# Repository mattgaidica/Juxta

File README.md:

# Juxta
 
__TI CCS Dev__

> Use LP_CC1352P7_4 projects for your CC2652P7 device.  This is also covered in the Running Software Examples on CC2652P module of the BLE5-Stack Migration Guide.  You still need an antenna switch to determine whether to use the normal or high-PA output path, although if using a custom design with one determined path then you can choose "Use Custom Board" and remove the CONFIG_RF_* pin assignments.

* In CCS > *.syscfg click the Board icon, select "Use custom board"
* Make a new target file for CC2652P7 and right-click it active

${COM_TI_SIMPLELINK_CC13XX_CC26XX_SDK_INSTALL_DIR_REPOS}

__Base SysConfig (no RF)__

		/**
	 * These arguments were used when this file was generated. They will be automatically applied on subsequent loads
	 * via the GUI or CLI. Run CLI with '--help' for additional information on how to override these arguments.
	 * @cliArgs --device "CC1352P7RGZ" --package "RGZ" --part "Default" --rtos "tirtos7" --product "simplelink_cc13xx_cc26xx_sdk@6.10.00.29"
	 * @versions {"tool":"1.12.0+2406"}
	 */
	
	/**
	 * Import the modules used in this configuration.
	 */
	const rfdesign    = scripting.addModule("/ti/devices/radioconfig/rfdesign");
	const ADC         = scripting.addModule("/ti/drivers/ADC", {}, false);
	const ADC1        = ADC.addInstance();
	const GPIO        = scripting.addModule("/ti/drivers/GPIO");
	const GPIO2       = GPIO.addInstance();
	const GPIO3       = GPIO.addInstance();
	const GPIO4       = GPIO.addInstance();
	const GPIO5       = GPIO.addInstance();
	const GPIO6       = GPIO.addInstance();
	const GPIO7       = GPIO.addInstance();
	const GPIO8       = GPIO.addInstance();
	const Power       = scripting.addModule("/ti/drivers/Power");
	const SPI         = scripting.addModule("/ti/drivers/SPI", {}, false);
	const SPI1        = SPI.addInstance();
	const Settings    = scripting.addModule("/ti/posix/tirtos/Settings");
	const BIOS        = scripting.addModule("/ti/sysbios/BIOS");
	const Event       = scripting.addModule("/ti/sysbios/knl/Event");
	const Idle        = scripting.addModule("/ti/sysbios/knl/Idle", {}, false);
	const Idle2       = Idle.addInstance();
	const Mailbox     = scripting.addModule("/ti/sysbios/knl/Mailbox");
	const Error       = scripting.addModule("/ti/sysbios/runtime/Error");
	const SysCallback = scripting.addModule("/ti/sysbios/runtime/SysCallback");
	const Timestamp   = scripting.addModule("/ti/sysbios/runtime/Timestamp");
	
	/**
	 * Write custom configuration values to the imported modules.
	 */
	rfdesign.fbSub1g = "none";
	rfdesign.fe24g   = "ID";
	rfdesign.pa20    = "none";
	
	ADC1.$name              = "VBATT";
	ADC1.adc.adcPin.$assign = "DIO_27";
	
	GPIO2.$name           = "LED_1";
	GPIO2.mode            = "Output";
	GPIO2.outputStrength  = "Low";
	GPIO2.gpioPin.$assign = "DIO_6";
	
	GPIO3.$name              = "AXY_CS";
	GPIO3.mode               = "Output";
	GPIO3.initialOutputState = "High";
	GPIO3.gpioPin.$assign    = "DIO_16";
	
	GPIO4.$name           = "AXY_INT";
	GPIO4.pull            = "Pull Up";
	GPIO4.gpioPin.$assign = "DIO_17";
	
	GPIO5.$name           = "DEBUG";
	GPIO5.gpioPin.$assign = "DIO_22";
	
	GPIO6.$name           = "Rx";
	GPIO6.gpioPin.$assign = "DIO_24";
	
	GPIO7.$name           = "Tx";
	GPIO7.mode            = "Output";
	GPIO7.gpioPin.$assign = "DIO_25";
	
	GPIO8.$name           = "LED_0";
	GPIO8.mode            = "Output";
	GPIO8.outputStrength  = "Low";
	GPIO8.gpioPin.$assign = "DIO_26";
	
	const CCFG              = scripting.addModule("/ti/devices/CCFG", {}, false);
	CCFG.ccfgTemplate.$name = "ti_devices_CCFG_CCFGCC26XXTemplate0";
	
	SPI1.$name               = "CONFIG_SPI";
	SPI1.spi.sclkPin.$assign = "DIO_19";
	SPI1.spi.misoPin.$assign = "DIO_20";
	SPI1.spi.mosiPin.$assign = "DIO_21";
	
	BIOS.assertsEnabled = false;
	BIOS.heapBaseAddr   = "__primary_heap_start__";
	BIOS.heapEndAddr    = "__primary_heap_end__";
	
	const Hwi           = scripting.addModule("/ti/sysbios/family/arm/m3/Hwi", {}, false);
	Hwi.enableException = false;
	
	const Clock      = scripting.addModule("/ti/sysbios/knl/Clock", {}, false);
	Clock.tickPeriod = 10;
	
	const Timer       = scripting.addModule("/ti/sysbios/family/arm/cc26xx/Timer", {}, false);
	Timer.rtc.$assign = "RTC0";
	
	Idle2.$name   = "powerIdle";
	Idle2.idleFxn = "Power_idleFunc";
	
	const Semaphore            = scripting.addModule("/ti/sysbios/knl/Semaphore", {}, false);
	Semaphore.supportsPriority = false;
	
	const Swi         = scripting.addModule("/ti/sysbios/knl/Swi", {}, false);
	Swi.numPriorities = 6;
	
	const Task             = scripting.addModule("/ti/sysbios/knl/Task", {}, false);
	Task.defaultStackSize  = 512;
	Task.idleTaskStackSize = 512;
	Task.numPriorities     = 6;
	
	Error.policy       = "Error_SPIN";
	Error.printDetails = false;
	
	const System           = scripting.addModule("/ti/sysbios/runtime/System", {}, false);
	System.abortFxn        = "System_abortSpin";
	System.exitFxn         = "System_exitSpin";
	System.extendedFormats = "%f";
	System.supportModule   = "SysCallback";
	
	/**
	 * Pinmux solution for unlocked pins/peripherals. This ensures that minor changes to the automatic solver in a future
	 * version of the tool will not impact the pinmux you originally saw.  These lines can be completely deleted in order to
	 * re-solve from scratch.
	 */
	ADC1.adc.$suggestSolution              = "ADC0";
	SPI1.spi.$suggestSolution              = "SSI0";
	SPI1.spi.dmaRxChannel.$suggestSolution = "DMA_CH3";
	SPI1.spi.dmaTxChannel.$suggestSolution = "DMA_CH4";

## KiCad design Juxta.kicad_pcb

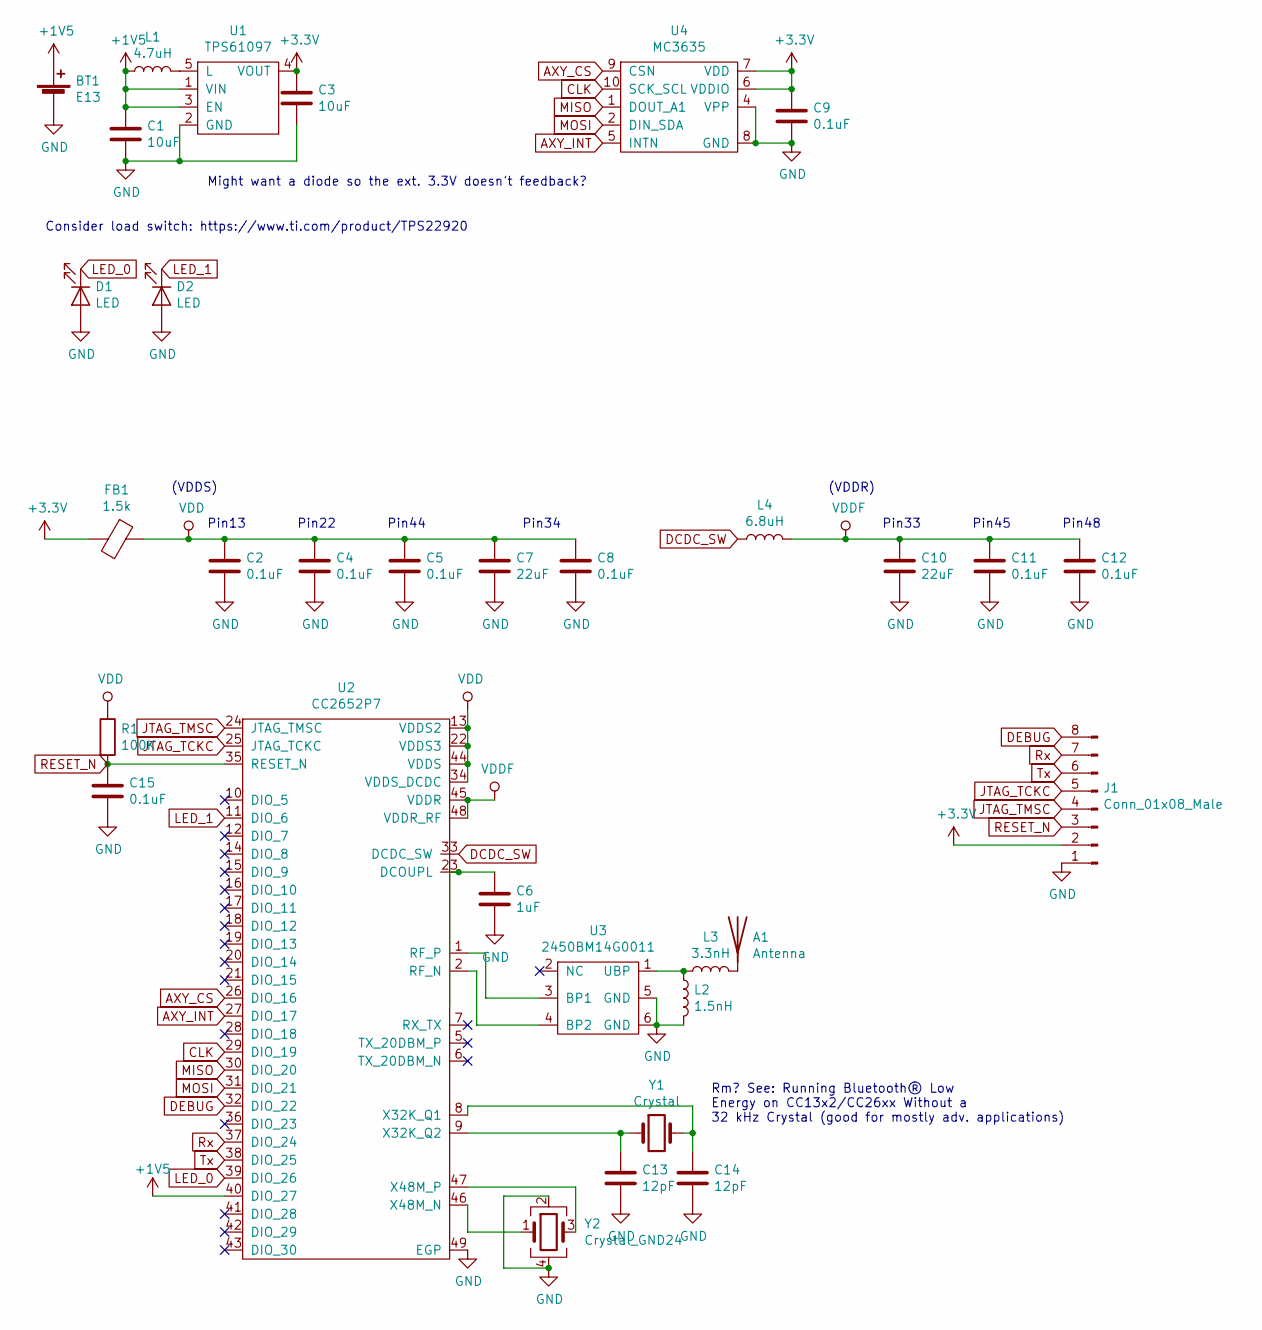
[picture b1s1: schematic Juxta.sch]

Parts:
A1: Antenna; 2450AT18B100; DigiKey 712-1006-1-ND
BT1: E13; 2988_7.9mmBatteryContact; DigiKey 36-2988CT-ND
C1, C3: 10uF; C_0402_1005Metric; DigiKey 13-CC0402MPX5R4BB106CT-ND
C2, C4, C5, C8, C9, C11, C12, C15: 0.1uF; C_0402_1005Metric; DigiKey 478-1126-1-ND
C6: 1uF; C_0402_1005Metric; DigiKey 478-4596-1-ND
C7, C10: 22uF; C_0402_1005Metric; DigiKey 478-04024D226MAT2ACT-ND
C13, C14: 12pF; C_0402_1005Metric; DigiKey 490-5924-2-ND
D1, D2: LED; LED_0402_1005Metric; DigiKey 1830-1056-1-ND
FB1: 1.5k; L_0402_1005Metric; DigiKey 445-2158-1-ND
J1: Conn_01x08_Male; Molex_SlimStack_502430-0820_2x04_P0.40mm_Vertical; Mouser 538-50243-00822
L1: 4.7uH; L_0603_1608Metric; DigiKey 445-6390-1-ND
L2: 1.5nH; L_0402_1005Metric; DigiKey 334-1083-1-ND
L3: 3.3nH; L_0402_1005Metric; DigiKey 490-6561-1-ND
L4: 6.8uH; L_0603_1608Metric; DigiKey 445-MLZ1608M6R8WT000CT-ND
R1: 100K; R_0402_1005Metric; DigiKey RMCF0402FT100KCT-ND
U1: TPS61097; SOT-23-5
U2: CC2652P7; QFN-48-1EP_7x7mm_P0.5mm_EP5.15x5.15mm
U3: 2450BM14G0011; DigiKey 712-1620-1-ND
U4: MC3635; LGA-10_1.6x1.6; DigiKey 2548-MC3635CT-ND
Y1: Crystal; Crystal_SMD_2012-2Pin_2.0x1.2mm; DigiKey SER4081TR-ND
Y2: Crystal_GND24; Crystal_SMD_2016-4Pin_2.0x1.6mm; DigiKey 535-13930-1-ND

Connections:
+1V5: BT1.1 (+), C1.1, L1.1, U1.1 (VIN), U1.3 (EN), U2.40 (DIO_27)
+3V3: C3.1, C9.1, FB1.2, J1.2, U1.4 (VOUT), U4.6 (VDDIO), U4.7 (VDD)
AXY_CS: U2.26 (DIO_16), U4.9 (CSN)
AXY_INT: U2.27 (DIO_17), U4.5 (INTN)
CLK: U2.29 (DIO_19), U4.10 (SCK_SCL)
DCDC_SW: L4.1, U2.33 (DCDC_SW)
DEBUG: J1.8, U2.32 (DIO_22)
GND: BT1.2 (-), C1.2, C2.2, C3.2, C4.2, C5.2, C6.2, C7.2, C8.2, C9.2, C10.2, C11.2, C12.2, C13.2, C14.2, C15.2, D1.2 (A), D2.2 (A), J1.1, L2.2, U1.2 (GND), U2.49 (EGP), U3.5 (GND), U3.6 (GND), U4.4 (VPP), U4.8 (GND), Y2.2, Y2.4
JTAG_TCKC: J1.5, U2.25 (JTAG_TCKC)
JTAG_TMSC: J1.4, U2.24 (JTAG_TMSC)
LED_0: D1.1 (K), U2.39 (DIO_26)
LED_1: D2.1 (K), U2.11 (DIO_6)
MISO: U2.30 (DIO_20), U4.1 (DOUT_A1)
MOSI: U2.31 (DIO_21), U4.2 (DIN_SDA)
unnamed: A1.1, L3.2
unnamed: C6.1, U2.23 (DCOUPL)
unnamed: C13.1, U2.9 (X32K_Q2), Y1.1
unnamed: C14.1, U2.8 (X32K_Q1), Y1.2
unnamed: L1.2, U1.5 (L)
unnamed: L2.1, L3.1, U3.1 (UBP)
unnamed: U2.1 (RF_P), U3.3 (BP1)
unnamed: U2.2 (RF_N), U3.4 (BP2)
unnamed: U2.46 (X48M_N), Y2.1
unnamed: U2.47 (X48M_P), Y2.3
RESET_N: C15.1, J1.3, R1.2, U2.35 (RESET_N)
Rx: J1.7, U2.37 (DIO_24)
Tx: J1.6, U2.38 (DIO_25)
VDD: C2.1, C4.1, C5.1, C7.1, C8.1, FB1.1, R1.1, U2.13 (VDDS2), U2.22 (VDDS3), U2.34 (VDDS_DCDC), U2.44 (VDDS)
VDDF: C10.1, C11.1, C12.1, L4.2, U2.45 (VDDR), U2.48 (VDDR_RF)

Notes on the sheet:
(VDDS)
(VDDR)
Pin33
Pin45
Pin48
Pin34
Pin44
Pin22
Pin13
Might want a diode so the ext. 3.3V doesn’t feedback?
Rm? See: Running Bluetooth® Low Energy on CC13x2/CC26xx Without a 32 kHz Crystal (good for mostly adv. applications)
Consider load switch: https://www.ti.com/product/TPS22920

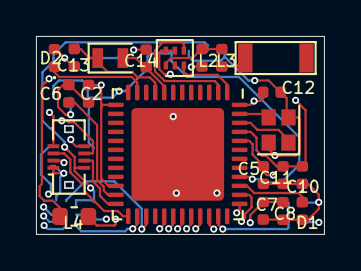
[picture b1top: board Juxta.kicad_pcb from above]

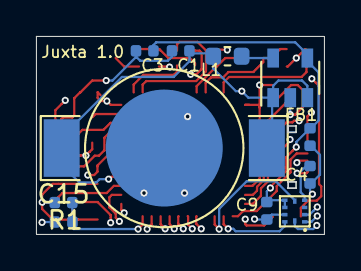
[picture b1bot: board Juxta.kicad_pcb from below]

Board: 4 copper layers, 15.9 x 11.0 mm, 32 parts (11 on the bottom side), 29 nets.
